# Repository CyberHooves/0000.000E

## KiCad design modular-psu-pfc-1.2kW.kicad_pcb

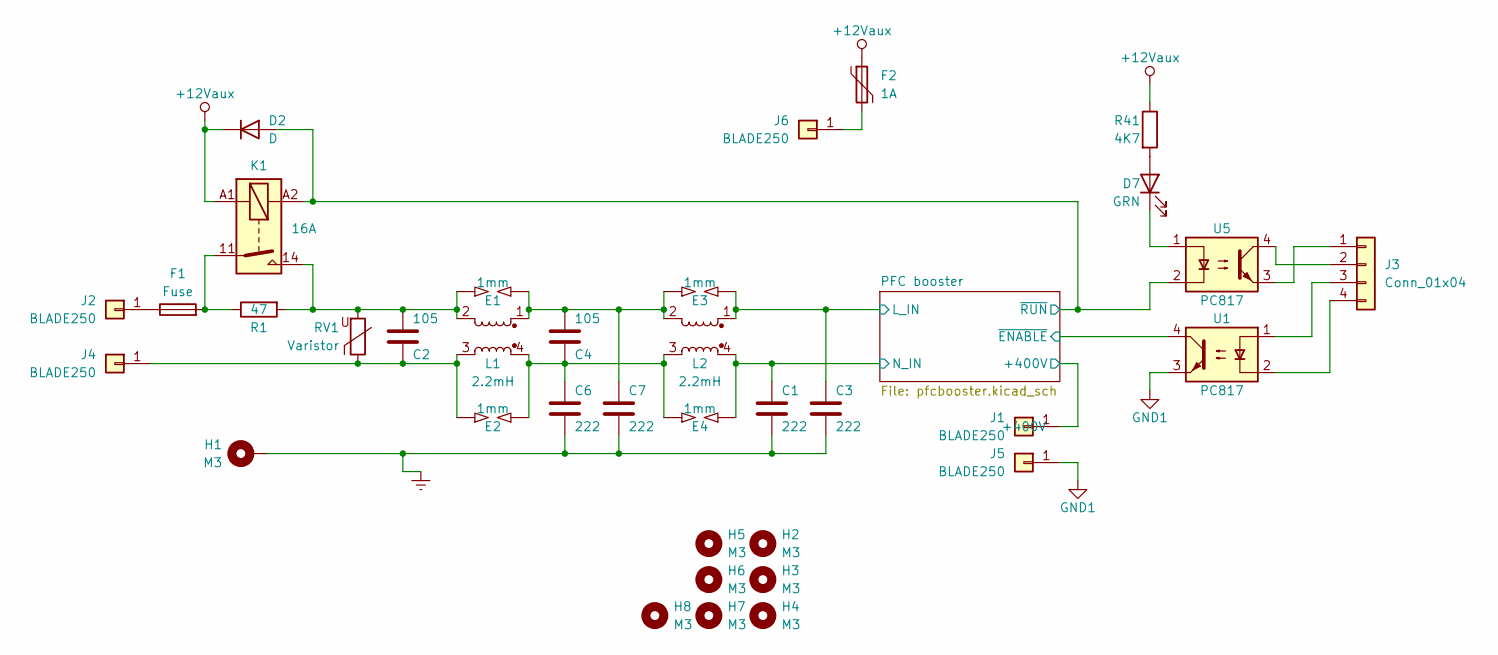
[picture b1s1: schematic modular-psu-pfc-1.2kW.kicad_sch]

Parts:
C1, C3, C6, C7: 222; C_Disc_D10.5mm_W5.0mm_P7.50mm
C2, C4: 105; C_Rect_L26.5mm_W11.5mm_P22.50mm_MKS4
D2: D; D_SOD-123
D7: GRN; LED_D3.0mm_Clear
E1, E2, E3, E4: 1mm; SG_6MM_3SPIKE_GAP1MM
F1: Fuse; Fuseholder_Clip-6.3x32mm_Littelfuse_102071_Inline_P34.70x7.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
F2: 1A; Fuse_1210_3225Metric
H1: M3; MountingHole_3.2mm_M3_Pad
H2, H3, H4, H5, H6, H7, H8: M3; MountingHole_3.2mm_M3
J1, J2, J4, J5, J6: BLADE250; CON-BLADE250-VERTICAL
J3: Conn_01x04; JST_XA_B04B-XASK-1-A_1x04_P2.50mm_Vertical
K1: 16A; Relay_1-Form-A_Schrack-RYII_RM5mm
L1, L2: 2.2mH; L_CommonMode_Toroid_Vertical_L30.5mm_W15.2mm_Px10.16mm_Py20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
R1: 47; R_Radial_Power_L12.0mm_W8.0mm_P5.00mm
R41: 4K7; R_0805_2012Metric
RV1: Varistor; RV_Disc_D21.5mm_W4.7mm_P10mm
U1, U5: PC817; DIP-4_W10.16mm

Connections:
+12Vaux: D2.1 (K), F2.1, K1.A1, R41.1; also elsewhere on the board
/PFC booster/+400V: J1.1; also elsewhere on the board
/PFC booster/L_IN: C3.1, E3.2, L2.1; also elsewhere on the board
/PFC booster/N_IN: C1.1, E4.2, L2.4; also elsewhere on the board
/PFC booster/~ENABLE: U1.4; also elsewhere on the board
/PFC booster/~RUN: D2.2 (A), K1.A2, U5.2; also elsewhere on the board
Earth: C1.2, C3.2, C6.2, C7.2, H1.1
GND1: J5.1, U1.3; also elsewhere on the board
unnamed: C2.2, E1.1, K1.14, L1.2, R1.2, RV1.2
unnamed: C4.1, C6.1, E2.2, E4.1, L1.4, L2.3
unnamed: C4.2, C7.1, E1.2, E3.1, L1.1, L2.2
unnamed: D7.2 (A), R41.2
unnamed: D7.1 (K), U5.1
unnamed: F1.2, K1.11, R1.1
unnamed: F1.1, J2.1
unnamed: J3.1, U5.3
unnamed: J3.2, U5.4
unnamed: J3.3, U1.1
unnamed: J3.4, U1.2
unnamed: C2.1, E2.1, J4.1, L1.3, RV1.1
unnamed: F2.2, J6.1

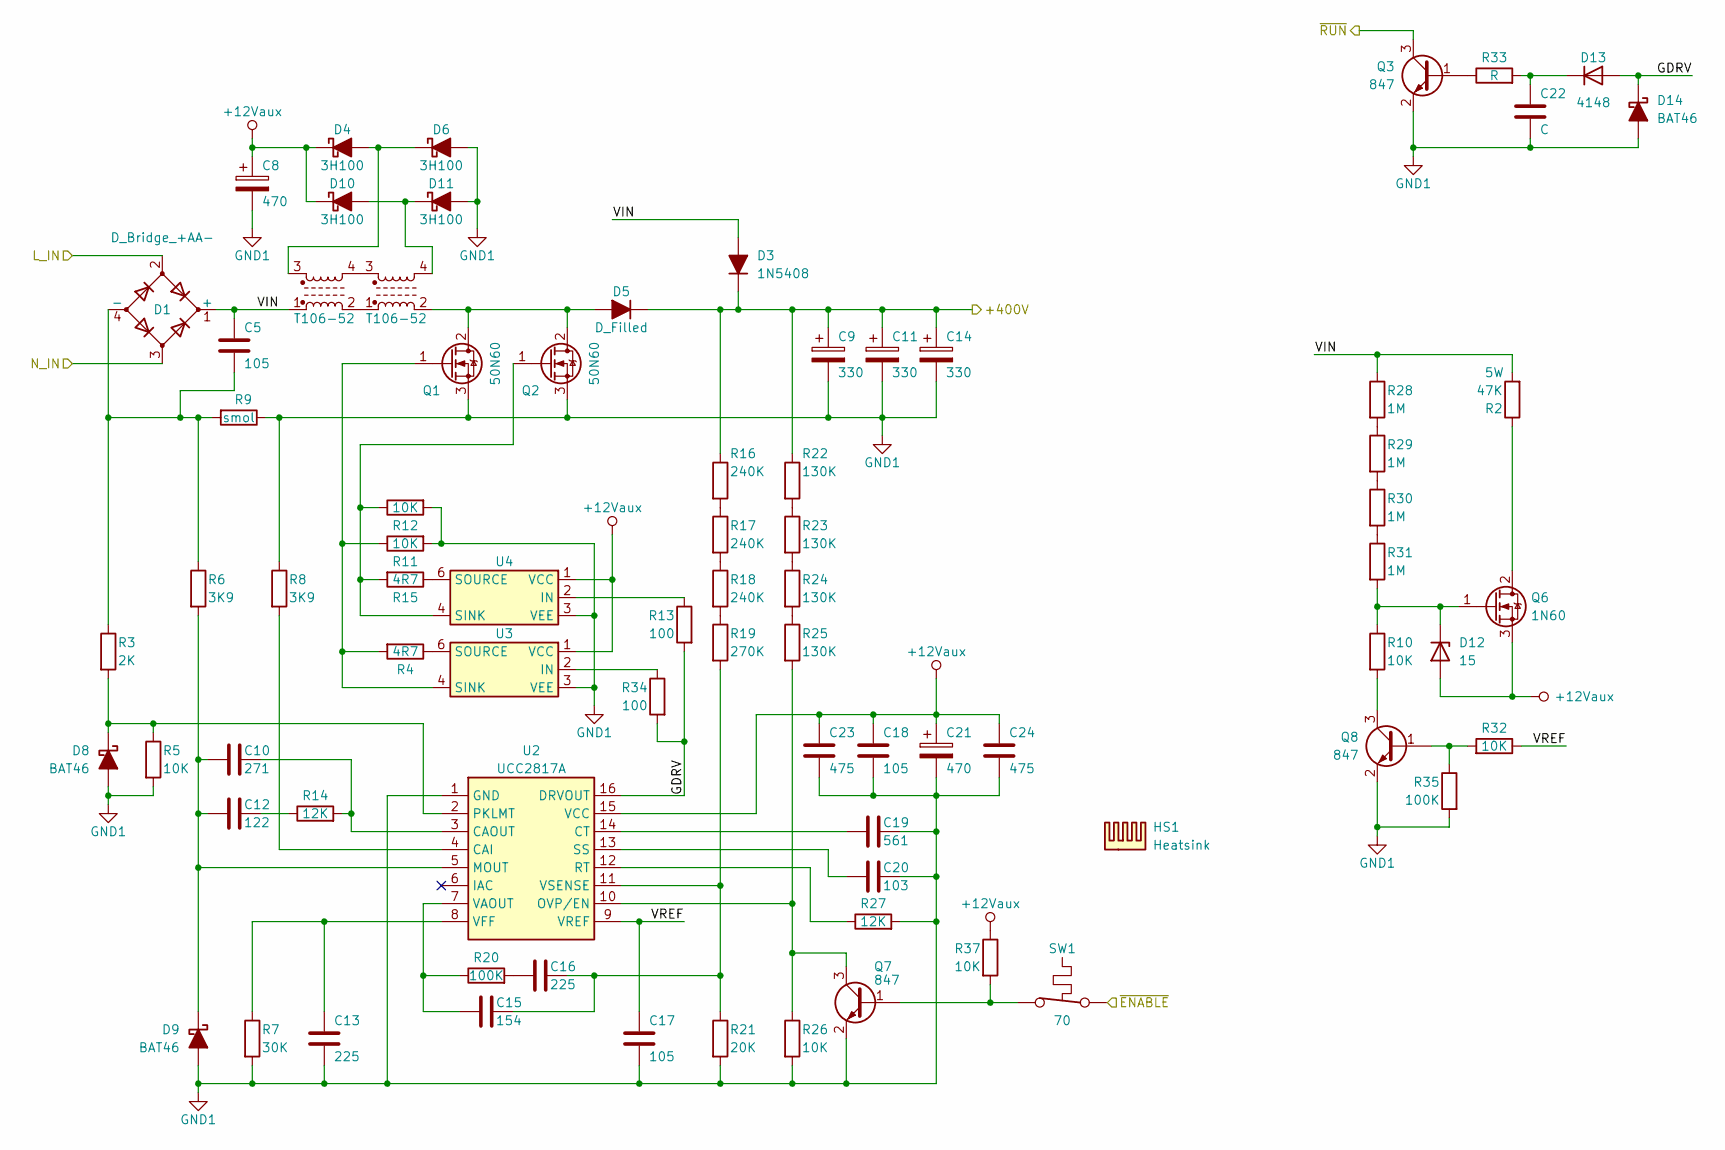
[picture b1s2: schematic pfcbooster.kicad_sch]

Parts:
C5: 105; C_Rect_L26.5mm_W11.5mm_P22.50mm_MKS4
C8, C21: 470; CP_Radial_D10.0mm_P5.00mm
C9, C11, C14: 330; CP_Radial_D30.0mm_P10.00mm_SnapIn
C10: 271; C_0805_2012Metric
C12: 122; C_0805_2012Metric
C13, C16: 225; C_0805_2012Metric
C15: 154; C_0805_2012Metric
C17, C18: 105; C_0805_2012Metric
C19: 561; C_0805_2012Metric
C20: 103; C_0805_2012Metric
C22: C; C_0805_2012Metric
C23, C24: 475; C_1210_3225Metric
D1: D_Bridge_+AA-; DIODE_BRIDGE_PB_VERTICAL
D3: 1N5408; D_SMC
D4, D6, D10, D11: 3H100; D_SMB
D5: D_Filled; TO-220-2_Vertical
D8, D9, D14: BAT46; D_SOD-123
D12: 15; D_SOD-123
D13: 4148; D_SOD-123
HS1: Heatsink; HS-FICSHER-SK499-60
L4, L5: T106-52; L_TOROID_D32_W18_4P_1
Q1, Q2: 50N60; TO-247-3_Vertical
Q3, Q7, Q8: 847; SOT-23
Q6: 1N60; TO-220-3_Vertical_Staggered
R2: 47K; R_Radial_Power_L12.0mm_W8.0mm_P5.00mm
R3: 2K; R_0805_2012Metric
R4, R15: 4R7; R_1210_3225Metric
R5, R10, R11, R12, R26, R32, R37: 10K; R_0805_2012Metric
R6, R8: 3K9; R_0805_2012Metric
R7: 30K; R_0805_2012Metric
R9: smol; TO-220-2_Vertical
R13, R34: 100; R_0805_2012Metric
R14, R27: 12K; R_0805_2012Metric
R16, R17, R18: 240K; R_1206_3216Metric
R19: 270K; R_1206_3216Metric
R20, R35: 100K; R_0805_2012Metric
R21: 20K; R_0805_2012Metric
R22, R23, R24, R25: 130K; R_1206_3216Metric
R28, R29, R30, R31: 1M; R_1206_3216Metric
R33: R; R_0805_2012Metric
SW1: 70; TO-220-2_Vertical
U2: UCC2817A; SOIC-16_3.9x9.9mm_P1.27mm
U3, U4: SOT-23-6

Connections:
+12Vaux: C8.1, C18.1, C21.1, C23.1, C24.1, D4.1 (K), D10.1 (K), D12.2 (A), Q6.3 (S), U2.15 (VCC), U3.1 (VCC), U4.1 (VCC); also elsewhere on the board
/PFC booster/+400V: C9.1, C11.1, C14.1, D3.1 (K), D5.1 (K), R16.1, R22.1; also elsewhere on the board
/PFC booster/GDRV: D13.2 (A), D14.1 (K), R13.2, R34.2, U2.16 (DRVOUT)
/PFC booster/L_IN: D1.2; also elsewhere on the board
/PFC booster/N_IN: D1.3; also elsewhere on the board
/PFC booster/VIN: C5.1, D1.1 (+), D3.2 (A), L4.1, R2.2, R28.1
/PFC booster/VREF: C17.1, R32.1, U2.9 (VREF)
/PFC booster/~ENABLE: SW1.1; also elsewhere on the board
/PFC booster/~RUN: Q3.3 (C); also elsewhere on the board
GND1: C8.2, C9.2, C11.2, C13.2, C14.2, C17.2, C18.2, C19.2, C20.2, C21.2, C22.2, C23.2, C24.2, D6.2 (A), D8.2 (A), D9.2 (A), D11.2 (A), D14.2 (A), Q1.3 (S), Q2.3 (S), Q3.2 (E), Q7.2 (E), Q8.2 (E), R5.2, R7.2, R8.1, R9.1, R11.2, R12.2, R21.2, R26.2, R27.2, R35.2, U2.1 (GND), U3.3 (VEE), U4.3 (VEE); also elsewhere on the board
unnamed: C12.2, R14.1
unnamed: C16.1, R20.2
unnamed: C5.2, D1.4 (-), R3.1, R6.1, R9.2
unnamed: D4.2 (A), D6.1 (K), L4.3
unnamed: D5.2 (A), L5.2, Q1.2 (D), Q2.2 (D)
unnamed: D8.1 (K), R3.2, R5.1, U2.2 (PKLMT)
unnamed: C10.1, C12.1, D9.1 (K), R6.2, U2.5 (MOUT)
unnamed: D10.2 (A), D11.1 (K), L5.4
unnamed: D12.1 (K), Q6.1 (G), R10.1, R31.2
unnamed: C22.1, D13.1 (K), R33.2
unnamed: L4.2, L5.1
unnamed: L4.4, L5.3
unnamed: Q1.1 (G), R4.2, R11.1, U3.4 (SINK)
unnamed: Q2.1 (G), R12.1, R15.2, U4.4 (SINK)
unnamed: Q3.1 (B), R33.1
unnamed: Q6.2 (D), R2.1
unnamed 40: Q7.1 (B), SW1.2; also elsewhere on the board
unnamed: Q7.3 (C), R25.2, R26.1, U2.10 (OVP/EN)
unnamed: Q8.1 (B), R32.2, R35.1
unnamed: Q8.3 (C), R10.2
unnamed: R16.2, R17.1
unnamed: R17.2, R18.1
unnamed: R18.2, R19.1
unnamed: R22.2, R23.1
unnamed: R23.2, R24.1
unnamed: R24.2, R25.1
unnamed: R28.2, R29.1
unnamed: R29.2, R30.1
unnamed: R30.2, R31.1
unnamed: R8.2, U2.4 (CAI)
unnamed: C10.2, R14.2, U2.3 (CAOUT)
unnamed: C19.1, U2.14 (CT)
unnamed: R27.1, U2.12 (RT)
unnamed: C20.1, U2.13 (SS)
unnamed: C15.1, R20.1, U2.7 (VAOUT)
unnamed: C13.1, R7.1, U2.8 (VFF)
unnamed: C15.2, C16.2, R19.2, R21.1, U2.11 (VSENSE)
unnamed: R34.1, U3.2 (IN)
unnamed: R4.1, U3.6 (SOURCE)
unnamed: R13.1, U4.2 (IN)
unnamed: R15.1, U4.6 (SOURCE)

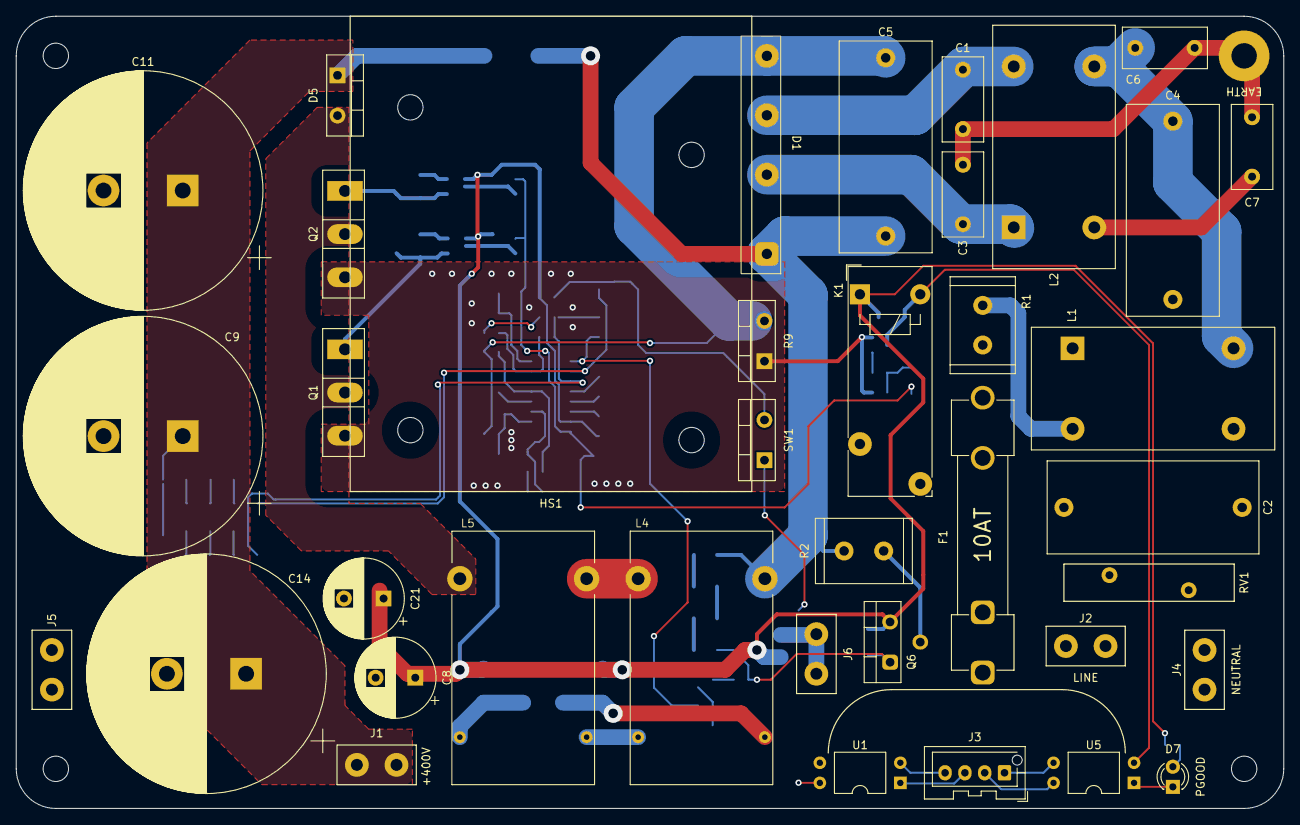
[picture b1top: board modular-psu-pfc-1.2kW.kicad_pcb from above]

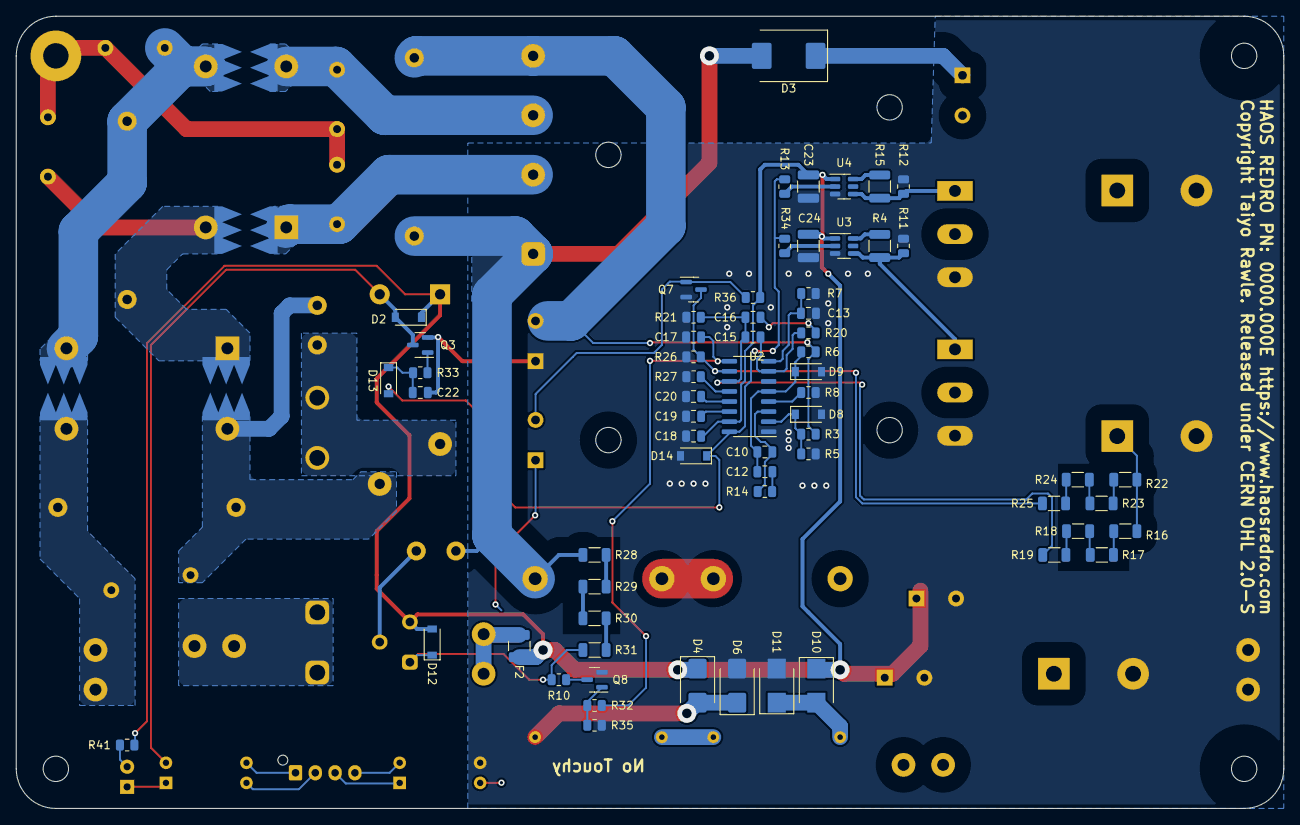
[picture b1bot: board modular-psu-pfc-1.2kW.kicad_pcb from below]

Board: 2 copper layers, 160.0 x 100.0 mm, 114 parts (68 on the bottom side), 65 nets.

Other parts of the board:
R36: 10K; R_0805_2012Metric

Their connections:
+12Vaux: R36.1; also elsewhere on the board
unnamed 40: R36.2; also elsewhere on the board

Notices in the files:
modular-psu-pfc-1.2kW.kicad_pcb:
Copyright Taiyo Rawle. Released under CERN OHL 2.0-S
